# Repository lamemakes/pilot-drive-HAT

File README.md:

# The hardware of PILOT Drive

This repo contains all of the hardware for PILOT Drive - mainly KiCad schematic + PCB files, and the code used for the ATtiny85 functionality.

## The PILOT Drive HAT MKII

(**TLDR**) The features of the HAT are:
- Optocouplers to isolate & read the ACC +12v & Headlight 12v+ lines
- Via I2C the Raspberry Pi communicates with the ATtiny85 to set the shutdown time
- When there is no ACC +12v detected from the Pi or the ATtiny, the Pi begins a safe shutdown and the ATtiny begins a countdown (Longer than it would take the Pi to shutdown) to kill the power to the BAT +12v. 
- The headlight detection optocoupler is connected to the RPi's GPIO pins
- An I2C connected RTC is included to allow the Pi to keep time without network connectivity.
- Input for general purpose external buttons
- (Mostly) Conforms to the standards of the [Raspberry Pi HAT specifications](https://github.com/raspberrypi/hats), as it includes an ID EEPROM and follows most design specs, but more needs to be implemented

### HAT MKI _[& lessons learned]_

The original MKI HAT came & went. I would call it about 50% functional - as it kept time well and provided for a clean way to route power to the Pi, along with interface with buttons. It didn't work for it's original purpose though. This was due to a few reasons:
- Using tantalum caps instead of electrolytic for the power supply
- Needed decoupling caps!
- Switching the entire ground via an N-FET. Speaks for itself.
- Needed TVS diodes!

# HAT MKII

The MKII prototype was fab'd by [PCBWay](https://www.pcbway.com/), and so far has proven to be fully functional! The new improvements did volumes for the usablity, debugging, and protection of the circuit & the Pi. If you're interested, come see it's debut at the 2023 Syracuse Maker Faire on April 1st!

_The Schematic of the HAT MKII_

_Fresh MKII proto boards_

_Populated MKII proto board_

## ATtiny85 Code

### C (current) version

Found in the "firmware" folder, the current C code is based on the ATtiny85 & it's Universal Serial Interface (USI). Using I2C, the Pi can communicate the the ATtiny (default slave address is 0x20) to send a **one byte** integer (<= 255). This single integer represents the time to wait before the ATtiny pulls the power on the entire circuit after it detects the vehicle power off.

As _always_ the firmware is a WIP, and the C version isn't fully functional. I can't quite clamp why, but at the time of writing the second ACK from the ATtiny (after the one byte int) always fails. Addressing works & ACKS, the ATtiny recieves the timeout number and functions with it, but the master sees it as a failed transmission. I feel like I'm close to a fix, but stuck now.

### Arduino (legacy) version

The original firmware was written in Arduino with TinyWireS, but I believed getting a little more "bare metal" would've allowed for a lot more (needed) C & embedded learning, and allowing for quick speeds. That code can be found under "legacy" in the "firmware" folder for use until the C version is completed & smoothed over.

### To flash to the ATtiny85

This firmware requires the [avrdude](https://github.com/avrdudes/avrdude) toolchain to flash the ATtiny. With avrdude installed and an ICSP programmer connected to your ATtiny & computer, the only step left is to configure the following Makefile variables:
- ```PORT```: The serial port the ICSP device is connected to, defaults to ```/dev/ttyUSB0```
- ```AVRDUDE_CONF```: The path to your avrdude config, defauls to ```/etc/avrdude/avrdude.conf```
- ```CLK_SPEED```: Only configure if using an ATtiny85 clock speed other than 8 MHz.

### To send a timeout from to the ATtiny

This will be integrated in the [PILOT Drive software](https://github.com/lamemakes/PILOT-Drive), but an extremely simple Python script can be made to send the required timeout to a specified address, as can be seen in the example below (tested on an RPi 4):

```
import smbus

addr = 0x20 # Send to address 0x20
time = 15   # A timeout of 15 seconds

bus = smbus.SMBus(1)

bus.write_byte(addr, time)
```

At the time of writing, this script will seemingly fail, as it can't recieve a proper ACK from the ATtiny. Regardless, the ATtiny will recieve the time and respond accordingly.

### To connect a Raspberry Pi to the DS1307 RTC

**NOTE**: This guide assumes I2C has been enabled via `sudo raspi-config`

To connect the Raspberry Pi to the HAT's I2C RTC, execute the following commands on the Pi:

```
echo -e "\n# Configure the DS1307 PILOT Drive HAT\ndtoverlay=i2c-rtc,ds1307" | sudo tee -a /boot/config.txt
sudo reboot
```

After reboot, continue with the following:
```
# Ensure a "UU" appears
sudo i2cdetect -y 1

# Remove fake-hwclock
sudo apt -y remove fake-hwclock
sudo update-rc.d -f fake-hwclock remove
```

In `/lib/udev/hwclock-set`, comment out the following lines:
```
if [ -e /run/systemd/system ] ; then
    exit 0
fi
```

Write to the hardware clock:
```
# Ensure date/time is correct
date

# Write to the RTC
sudo hwclock -w

# Ensure hardware clock is correct
sudo hwclock -r
```

## NOTES:

- If building the HAT, "ID EEPROM" is recommended by Raspberry Pi [Hat Standards](https://github.com/raspberrypi/hats/blob/master/designguide.md) but aren't required to make the circuit function.
- The schematic's +5v screw terminal in refers to an external 12v to 5v buck converter. 
- KiCad library files are coming, along with 3D files for the components.
- If you're building this HAT or something similar, reach out! Would love to hear your stories.

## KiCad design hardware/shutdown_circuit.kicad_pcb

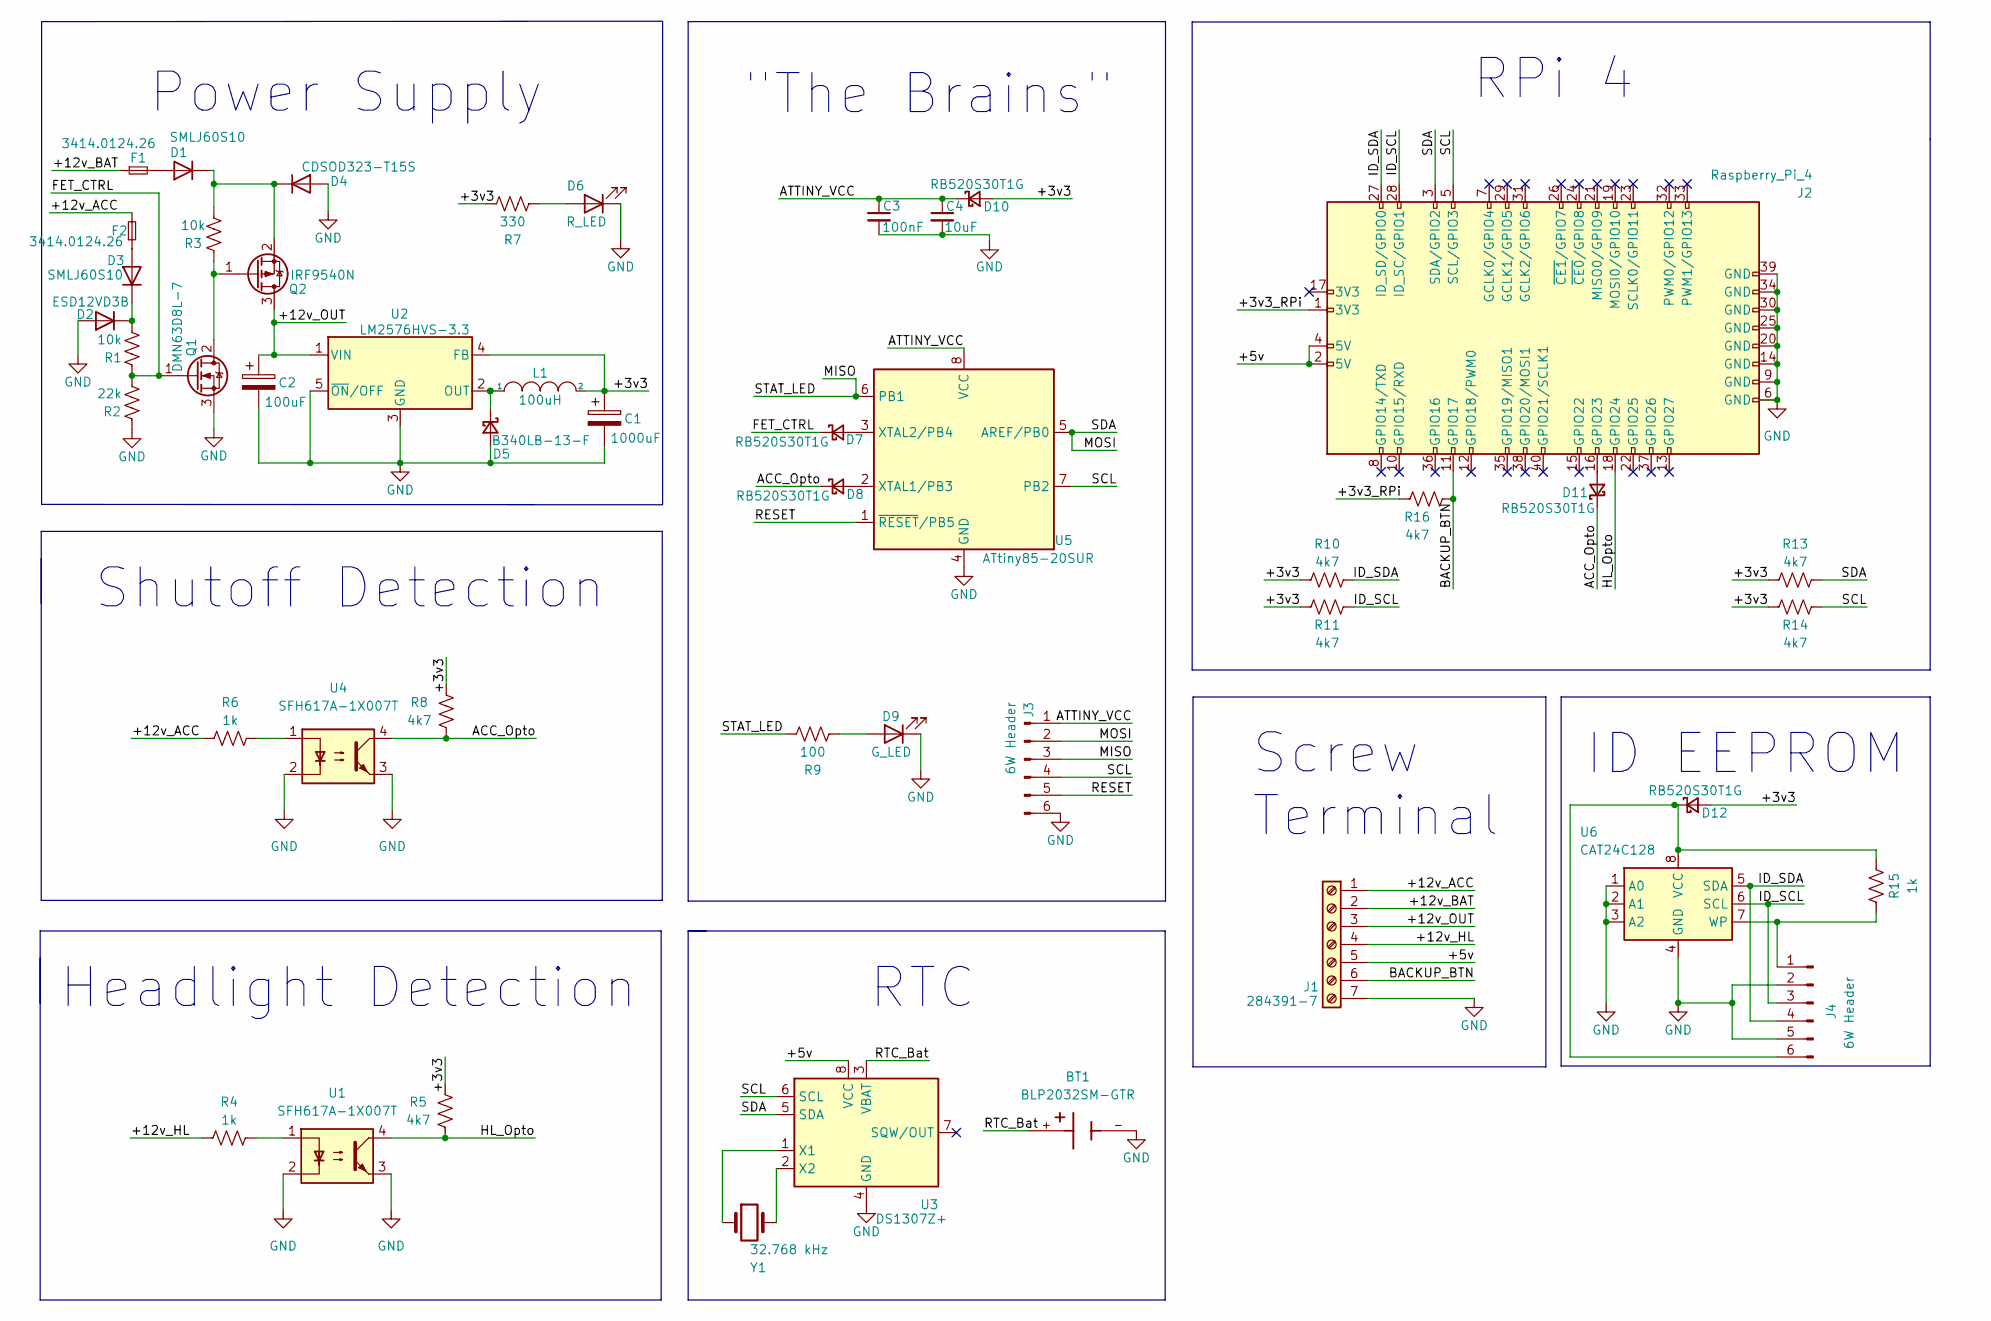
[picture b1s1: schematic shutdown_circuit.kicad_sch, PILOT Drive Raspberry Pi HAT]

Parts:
BT1: BLP2032SM-GTR; RTC_Battery_Holder; PARTREV J
C1: 1000uF; 1000uF_10v
C2: 100uF; 100uF_35v
C3: 100nF; C_0402_1005Metric_Pad0.74x0.62mm_HandSolder
C4: 10uF; C_0402_1005Metric_Pad0.74x0.62mm_HandSolder
D1, D3: SMLJ60S10; D_SMC_Handsoldering
D2: ESD12VD3B; D_SOD-323
D4: CDSOD323-T15S; D_SOD-323F
D5: B340LB-13-F; D_SMC_Handsoldering
D6: R_LED; LED_0603_1608Metric_Pad1.05x0.95mm_HandSolder
D7, D8, D10, D11, D12: RB520S30T1G; 3v3_TVS
D9: G_LED; LED_0603_1608Metric_Pad1.05x0.95mm_HandSolder
F1, F2: 3414.0124.26; Fuse_0402_1005Metric_Pad0.77x0.64mm_HandSolder
J1: 284391-7; Screw_Term
J2: Raspberry_Pi_4; PinSocket_2x20_P2.54mm_Vertical
J3, J4: 6W Header; PinHeader_1x06_P2.54mm_Vertical
L1: 100uH; 100uH_Inductor
Q1: DMN63D8L-7; N_FET
Q2: IRF9540N; P_FET
R1, R3: 10k; R_0402_1005Metric_Pad0.72x0.64mm_HandSolder
R2: 22k; R_0402_1005Metric_Pad0.72x0.64mm_HandSolder
R4, R6, R15: 1k; R_0402_1005Metric_Pad0.72x0.64mm_HandSolder
R5, R8, R10, R11, R13, R14, R16: 4k7; R_0402_1005Metric_Pad0.72x0.64mm_HandSolder
R7: 330; R_0402_1005Metric_Pad0.72x0.64mm_HandSolder
R9: 100; R_0402_1005Metric_Pad0.72x0.64mm_HandSolder
U1, U4: SFH617A-1X007T; Optocoupler
U2: LM2576HVS-3.3; TO-263-5_TabPin3
U3: DS1307Z+; DS1307Z+T&R
U5: ATtiny85-20SUR; ATTINY_SUR
U6: CAT24C128; CAT24C128YI
Y1: 32.768 kHz; RTC_Crystal

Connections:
/+3v3: C1.1, D10.2 (A), D12.2 (A), L1.2, R5.1, R7.1, R8.1, R10.2, R11.2, R13.2, R14.2, U2.4 (FB)
/+3v3_RPi: J2.1 (3V3), R16.1
/+5v: J1.5, J2.2 (5V), J2.4 (5V), U3.8 (VCC)
/+12v_ACC: F2.2, J1.1, R6.1
/+12v_BAT: F1.1, J1.2
/+12v_HL: J1.4, R4.1
/+12v_OUT: C2.1, J1.3, Q2.3 (D), U2.1 (VIN)
/ACC_Opto: D8.1 (K), D11.1 (K), R8.2, U4.4
/ATTINY_VCC: C3.1, C4.1, D10.1 (K), J3.1, U5.8 (VCC)
/BACKUP_BTN: J1.6, J2.11 (GPIO17), R16.2
/FET_CTRL: D7.1 (K), Q1.1 (G), R1.1, R2.2
/HL_Opto: J2.18 (GPIO24), R5.2, U1.4
/ID_SCL: J2.28 (ID_SC/GPIO1), J4.3, R11.1, U6.6 (SCL)
/ID_SDA: J2.27 (ID_SD/GPIO0), J4.4, R10.1, U6.5 (SDA)
/MISO: J3.3, R9.1, U5.6 (PB1)
/MOSI: J2.3 (SDA/GPIO2), J3.2, R13.1, U3.5 (SDA), U5.5 (AREF/PB0)
/RESET: J3.5, U5.1 (~RESET/PB5)
/RTC_Bat: BT1.+, U3.3 (VBAT)
/SCL: J2.5 (SCL/GPIO3), J3.4, R14.1, U3.6 (SCL), U5.7 (PB2)
GND: BT1.-, C1.2, C2.2, C3.2, C4.2, D2.2 (A), D4.2 (A), D5.2 (A), D6.1 (K), D9.1 (K), J1.7, J2.6 (GND), J2.9 (GND), J2.14 (GND), J2.20 (GND), J2.25 (GND), J2.30 (GND), J2.34 (GND), J2.39 (GND), J3.6, J4.2, J4.5, Q1.3 (S), R2.1, U1.2, U1.3, U2.3 (GND), U2.5 (~ON/OFF), U3.4 (GND), U4.2, U4.3, U5.4 (GND), U6.1 (A0), U6.2 (A1), U6.3 (A2), U6.4 (GND)
unnamed: D1.1 (K), D4.1 (K), Q2.2 (S), R3.2
unnamed: D1.2 (A), F1.2
unnamed: D2.1 (K), D3.1 (K), R1.2
unnamed: D3.2 (A), F2.1
unnamed: D5.1 (K), L1.1, U2.2 (OUT)
unnamed: D6.2 (A), R7.2
unnamed: D7.2 (A), U5.3 (XTAL2/PB4)
unnamed: D8.2 (A), U5.2 (XTAL1/PB3)
unnamed: D9.2 (A), R9.2
unnamed: D11.2 (A), J2.16 (GPIO23)
unnamed: D12.1 (K), J4.6, R15.2, U6.8 (VCC)
unnamed: J4.1, R15.1, U6.7 (WP)
unnamed: Q1.2 (D), Q2.1 (G), R3.1
unnamed: R4.2, U1.1
unnamed: R6.2, U4.1
unnamed: U3.1 (X1), Y1.1
unnamed: U3.2 (X2), Y1.2

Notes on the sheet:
Headlight Detection
RTC
Power Supply
ID EEPROM
Shutoff Detection
Screw Terminal
"The Brains"
RPi 4

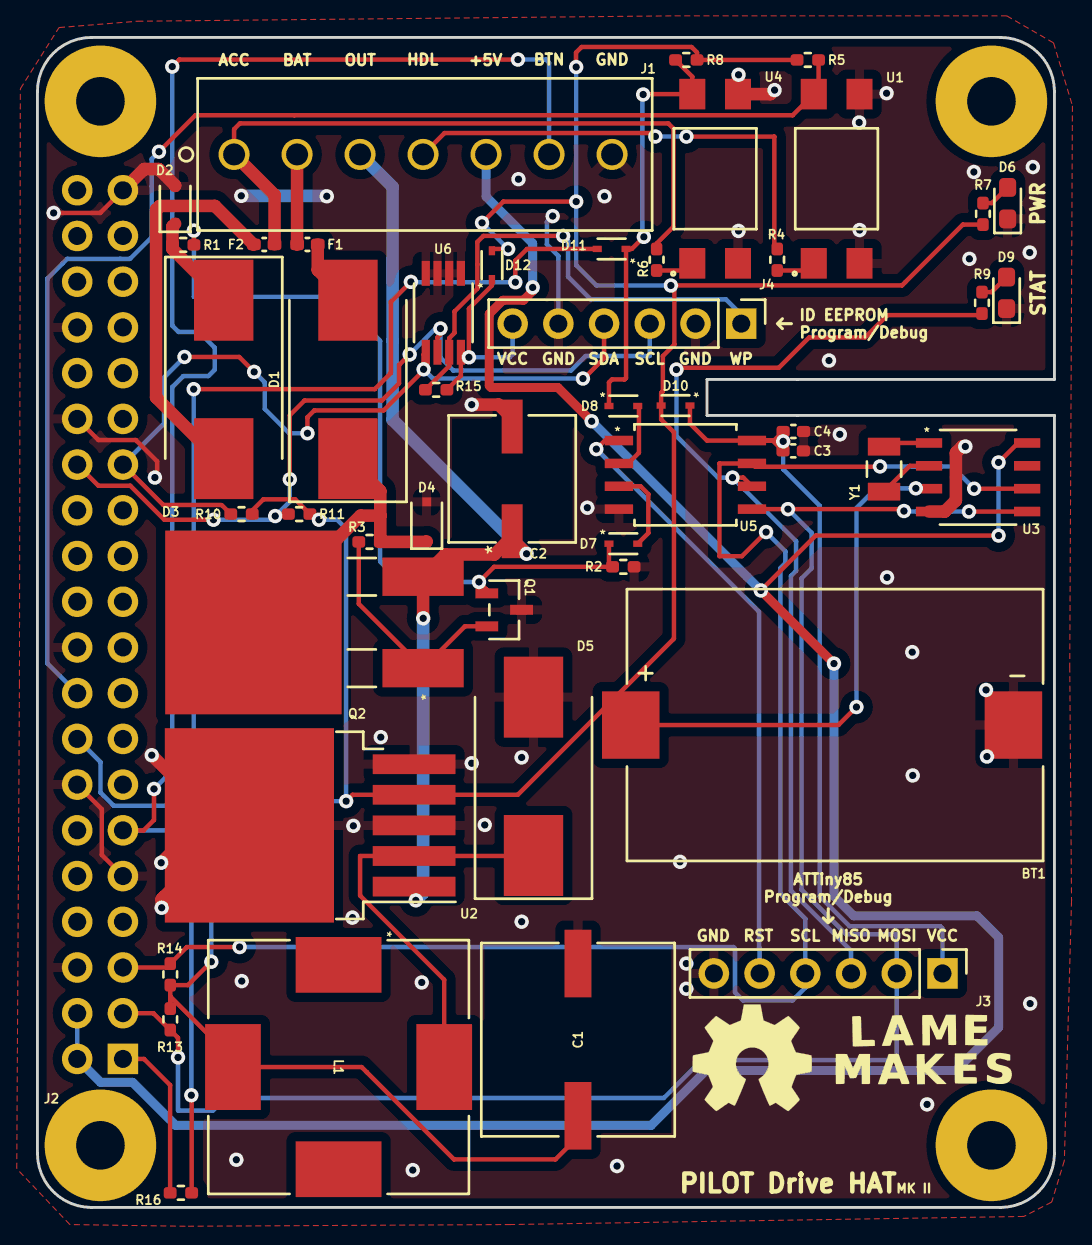
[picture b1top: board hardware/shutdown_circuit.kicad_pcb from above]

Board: 2 copper layers, 56.5 x 65.0 mm, 48 parts (1 on the bottom side), 37 nets.

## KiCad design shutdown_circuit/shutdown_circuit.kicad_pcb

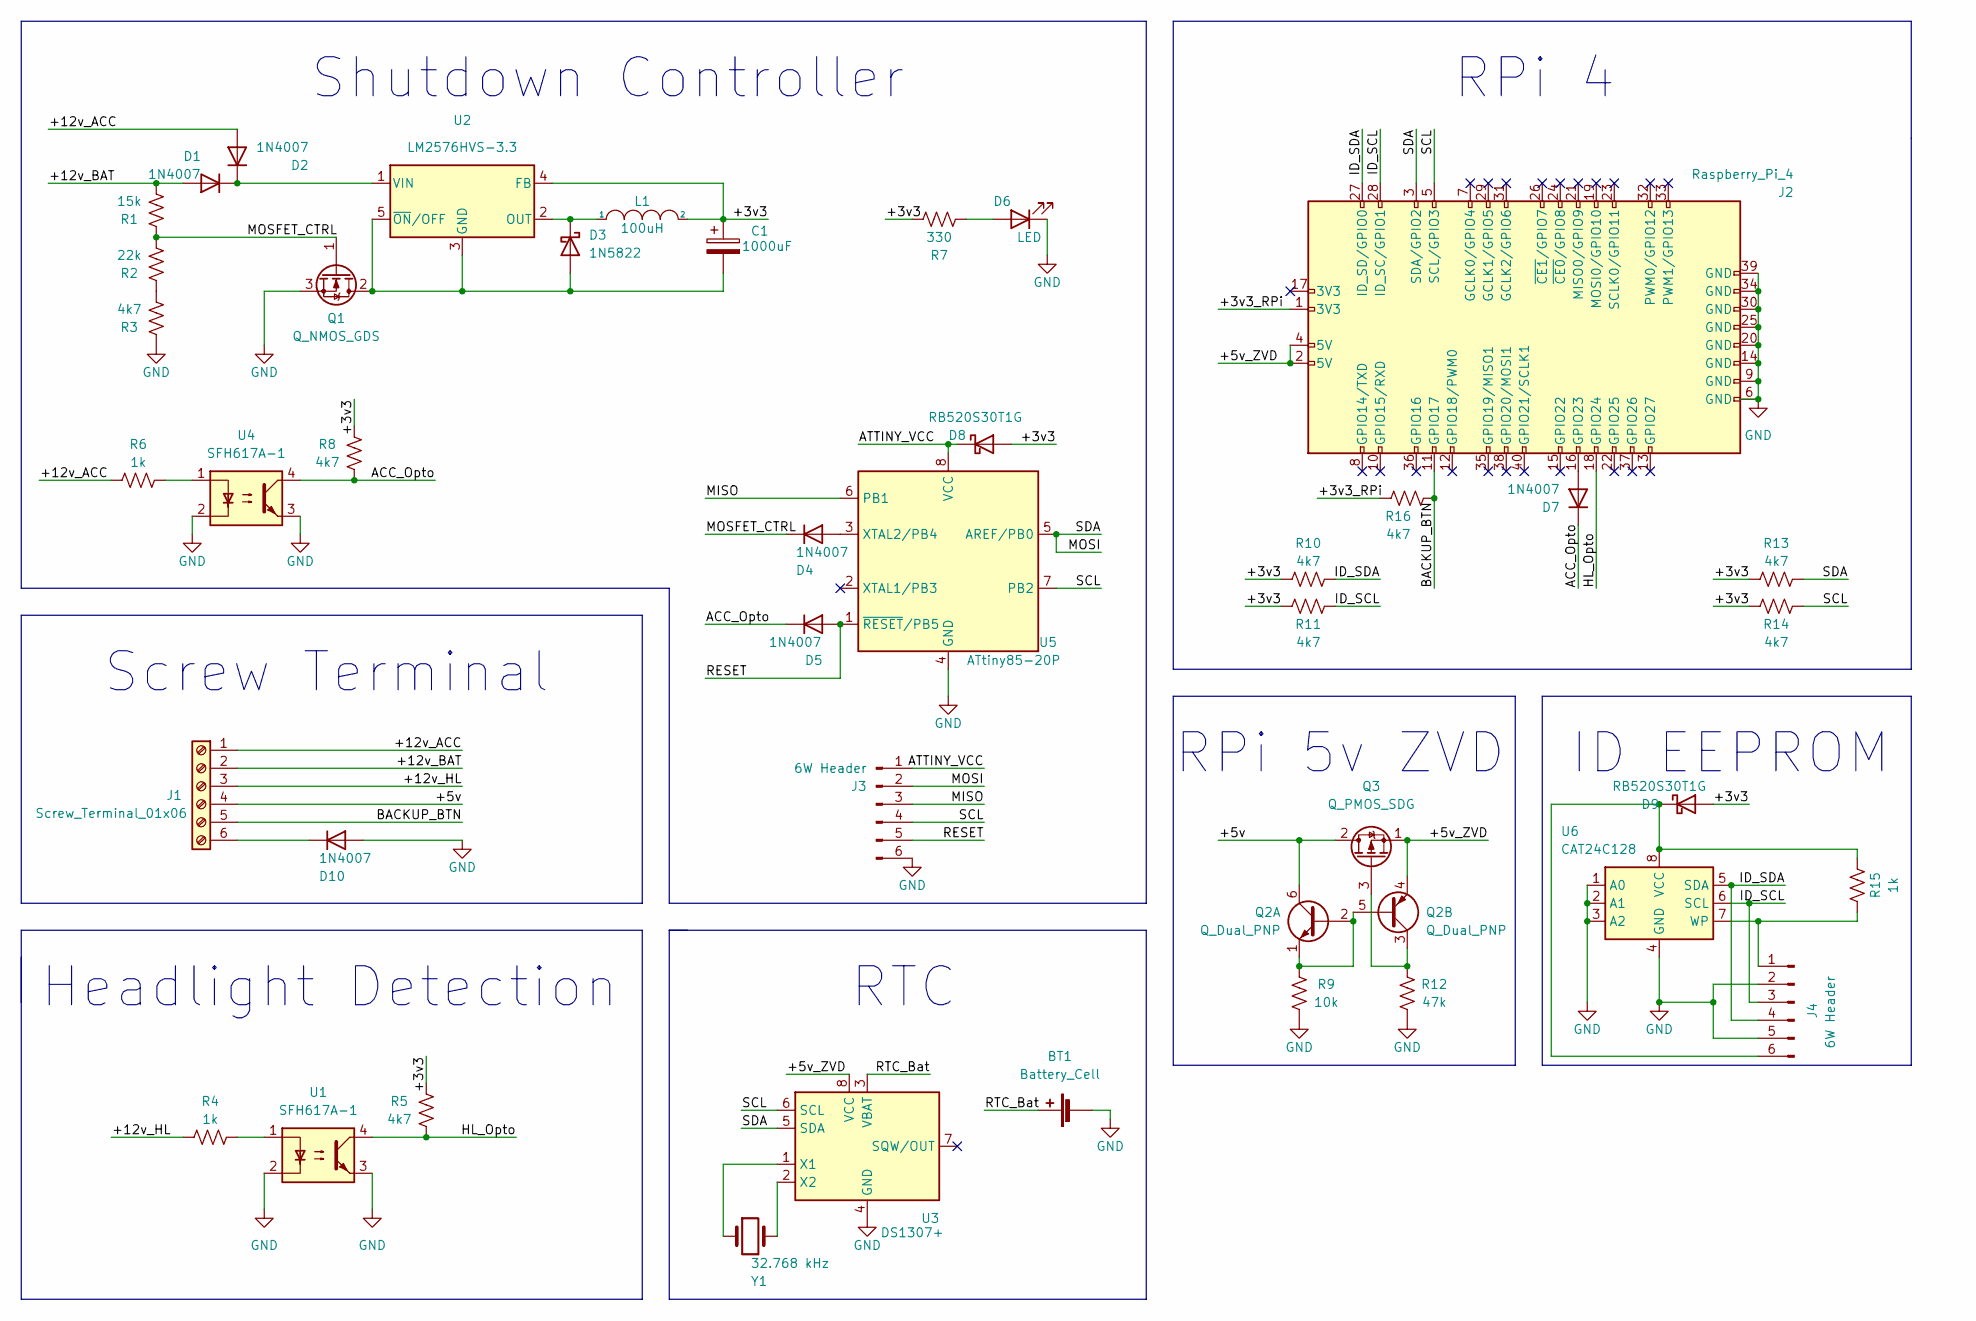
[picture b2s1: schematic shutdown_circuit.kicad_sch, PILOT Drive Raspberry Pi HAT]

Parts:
BT1: Battery_Cell; BatteryHolder_Keystone_106_1x20mm
C1: 1000uF; 100uF_Cap
D1, D2, D4, D5, D7, D10: 1N4007; 1N4007FLTR
D3: 1N5822; 1N4007FLTR
D6: LED; LED_0603_1608Metric_Pad1.05x0.95mm_HandSolder
D8, D9: RB520S30T1G; schottky_diodes
J1: Screw_Terminal_01x06; screw_term_6
J2: Raspberry_Pi_4; PinSocket_2x20_P2.54mm_Vertical
J3, J4: 6W Header; PinHeader_1x06_P2.54mm_Vertical
L1: 100uH; induct_100uH
Q1: Q_NMOS_GDS; TO-220-3_Vertical
Q2: Q_Dual_PNP; pnp_pair
Q3: Q_PMOS_SDG; zvd_mosfet
R1: 15k; R_0603_1608Metric_Pad0.98x0.95mm_HandSolder
R2: 22k; R_0603_1608Metric_Pad0.98x0.95mm_HandSolder
R3, R5, R8, R10, R11, R13, R14, R16: 4k7; R_0603_1608Metric_Pad0.98x0.95mm_HandSolder
R4, R6, R15: 1k; R_0603_1608Metric_Pad0.98x0.95mm_HandSolder
R7: 330; R_0603_1608Metric_Pad0.98x0.95mm_HandSolder
R9: 10k; R_0603_1608Metric_Pad0.98x0.95mm_HandSolder
R12: 47k; R_0603_1608Metric_Pad0.98x0.95mm_HandSolder
U1, U4: SFH617A-1; DIP-4_W7.62mm
U2: LM2576HVS-3.3; TO-263-5_TabPin3
U3: DS1307+; DIP-8_W7.62mm
U5: ATtiny85-20P; SOIC-8W_5.3x5.3mm_P1.27mm
U6: CAT24C128; TSSOP-8_4.4x3mm_P0.65mm
Y1: 32.768 kHz; Crystal_SMD_3215-2Pin_3.2x1.5mm

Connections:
/+3v3: C1.1, D8.2 (A), D9.2 (A), L1.2, R5.1, R7.1, R8.1, R10.2, R11.2, R13.2, R14.2, U2.4 (FB)
/+3v3_RPi: J2.1 (3V3), R16.1
/+5v: J1.4, Q2.6 (C1), Q3.2 (D)
/+5v_ZVD: J2.2 (5V), J2.4 (5V), Q2.4 (E2), Q3.1 (S), U3.8 (VCC)
/+12v_ACC: D2.2 (A), J1.1, R6.1
/+12v_BAT: D1.2 (A), J1.2, R1.2
/+12v_HL: J1.3, R4.1
/ACC_Opto: D5.1 (K), D7.1 (K), R8.2, U4.4
/ATTINY_VCC: D8.1 (K), J3.1, U5.8 (VCC)
/BACKUP_BTN: J1.5, J2.11 (GPIO17), R16.2
/HL_Opto: J2.18 (GPIO24), R5.2, U1.4
/ID_SCL: J2.28 (ID_SC/GPIO1), J4.3, R11.1, U6.6 (SCL)
/ID_SDA: J2.27 (ID_SD/GPIO0), J4.4, R10.1, U6.5 (SDA)
/MISO: J3.3, U5.6 (PB1)
/MOSFET_CTRL: D4.1 (K), Q1.1 (G), R1.1, R2.2
/RESET: D5.2 (A), J3.5, U5.1 (~RESET/PB5)
/RTC_Bat: BT1.1 (+), U3.3 (VBAT)
/SCL: J2.5 (SCL/GPIO3), J3.4, R14.1, U3.6 (SCL), U5.7 (PB2)
/SDA: J2.3 (SDA/GPIO2), J3.2, R13.1, U3.5 (SDA), U5.5 (AREF/PB0)
GND: BT1.2 (-), D6.1 (K), D10.2 (A), J2.6 (GND), J2.9 (GND), J2.14 (GND), J2.20 (GND), J2.25 (GND), J2.30 (GND), J2.34 (GND), J2.39 (GND), J3.6, J4.2, J4.5, Q1.3 (S), R3.1, R9.2, R12.2, U1.2, U1.3, U3.4 (GND), U4.2, U4.3, U5.4 (GND), U6.1 (A0), U6.2 (A1), U6.3 (A2), U6.4 (GND)
unnamed: C1.2, D3.2 (A), Q1.2 (D), U2.3 (GND), U2.5 (~ON/OFF)
unnamed: D1.1 (K), D2.1 (K), U2.1 (VIN)
unnamed: D3.1 (K), L1.1, U2.2 (OUT)
unnamed: D4.2 (A), U5.3 (XTAL2/PB4)
unnamed: D6.2 (A), R7.2
unnamed: D7.2 (A), J2.16 (GPIO23)
unnamed: D9.1 (K), J4.6, R15.2, U6.8 (VCC)
unnamed: D10.1 (K), J1.6
unnamed: J4.1, R15.1, U6.7 (WP)
unnamed: Q2.1 (E1), Q2.2 (B1), Q2.5 (B2), R9.1
unnamed: Q2.3 (C2), Q3.3 (G), R12.1
unnamed: R2.1, R3.2
unnamed: R4.2, U1.1
unnamed: U3.1 (X1), Y1.1
unnamed: U3.2 (X2), Y1.2
unnamed: R6.2, U4.1

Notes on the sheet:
Headlight Detection
RTC
Shutdown Controller
ID EEPROM
RPi 5v ZVD
Screw Terminal
RPi 4

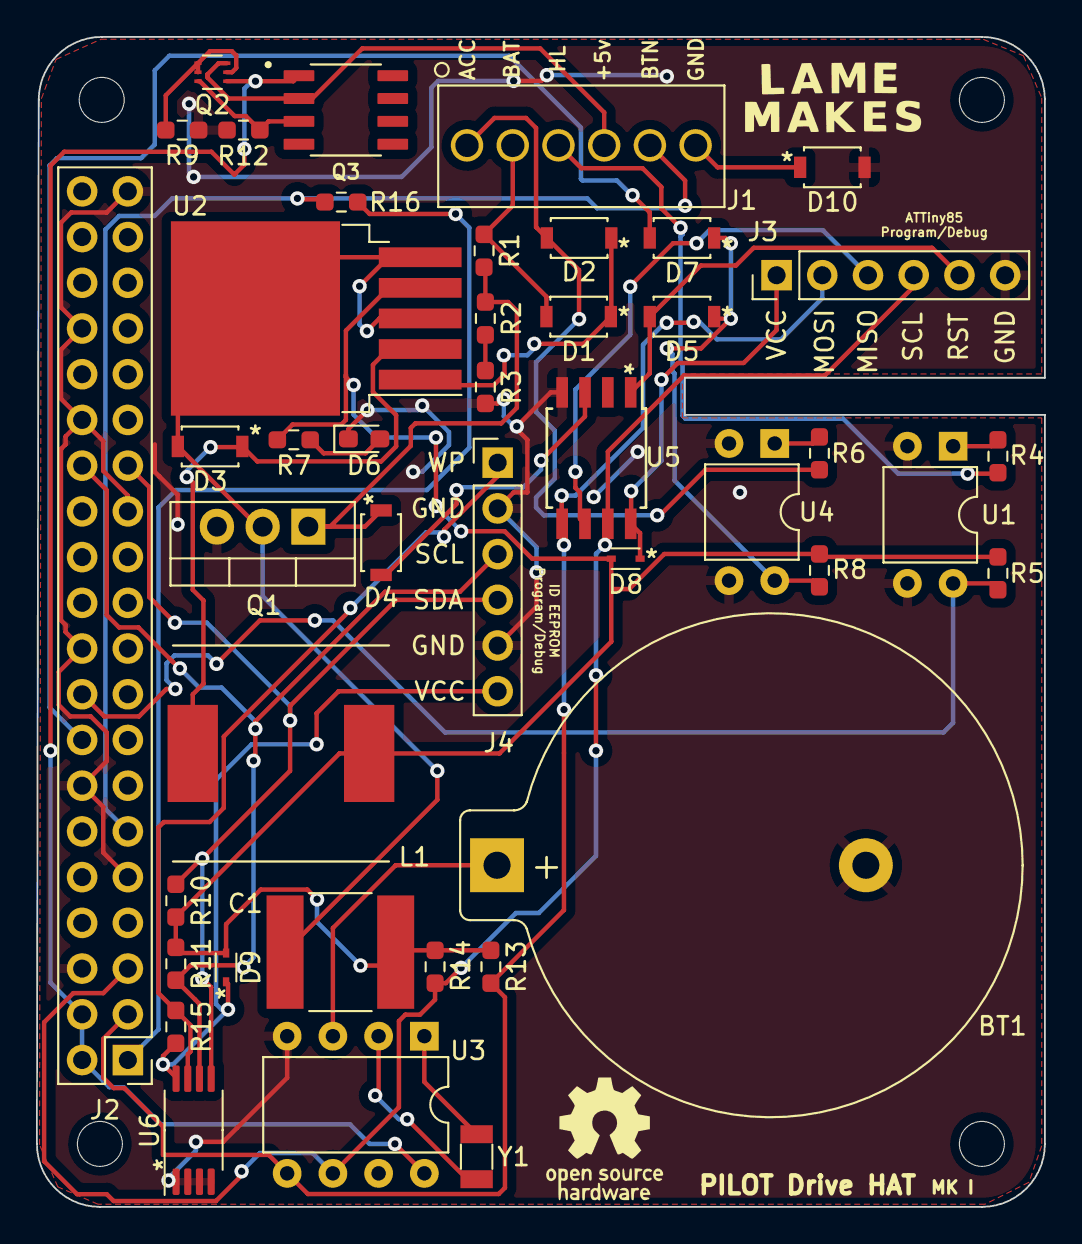
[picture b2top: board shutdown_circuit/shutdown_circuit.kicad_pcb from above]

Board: 2 copper layers, 56.0 x 65.0 mm, 43 parts (0 on the bottom side), 36 nets.

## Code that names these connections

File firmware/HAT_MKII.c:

#include <avr/io.h>PORTB
#include <avr/interrupt.h>
#include <util/delay.h>
#include "HAT_MKII.h"


/*
PB4 = MOSFET control (high is powered, low kills the circuit)   | Output
PB3 = Accessory Wire Optocoupler (pulled low when active)       | Input
PB2 = SCL                                                       | Input
PB1 = Status LED                                                | Output
PB0 = SDA                                                       | Input

INIT_DDRB shifts bits accordingly to input/output.
*/


void led_blink(int ledPb, int times){
    for (int i = 0; i < times; i++){
        PORTB ^= (1 << ledPb);
        _delay_ms(500);
        PORTB ^= (1 << ledPb);
        _delay_ms(500);
    }
}

void initialize()
{
    // Setup the needed PILOT Drive HAT pins
    DDRB = initDDRB;
    PORTB = (1 << FET_CTL) | (1 << ACC_OPTO); // Pullup ACC optocoupler pin & power the FET.

    // Setup I2C in the USI interface
    USICR = (1 << USIWM1) | (1 << USICS0) | (1 << USICS1);  // Set USI interface to I2C, and clock to external w negative edge sampling.
    //DDRB &= (1 << 2) | (1 << 0); // SDA & SCL direction as input

    led_blink(STATUS_LED, 1);
}

void send_ack() {
    USISR |= (1 << USIOIF);
    DDRB |= (1 << 0);  // Initialize the SDA Data Direction Bit
    int clkMask = (1 << USICNT3) | (1 << USICNT2) | (1 << USICNT1) | (1 << USICNT0);
    if (!byte) {    // If this is the first byte...
        USISR &= clkMask;
        while ((USISR & clkMask) <= (1 << USICNT2)) { // While the counter is <= 4, BUT greater than 2. An extra clock cycle is missed with the address bits, not sure why? Maybe start cond?
            if (USISR & clkMask >= (1 << USICNT1)){
                PORTB |= (1 << SDA); // Drive SDA
            }
        }
    } else if (byte > 0) {
        USISR &= clkMask;
        while ((USISR & clkMask) < (1 << 0)) { // While the counter is < 1
            PORTB |= (1 << SDA); // Drive SDA
        }
    }
    //PORTB &= ~(1 << 0); // Stop SDA drive & change data direction
    DDRB &= ~(1 << 0);
    USISR = 0; // Reset counter
}

void recieve_data(){
    int dataIn = USIBR / 2; // It appears the external clock is sampled on BOTH (pos/neg) edges, thus gets double the intended value?
    if (!byte && (dataIn == SLAVE_ADDR)){ // If this is the first byte & the buffer == slave address...
        read_data = 1;  // Set data read to true.
        send_ack();
    } else if (byte){
        timeout = dataIn;
        send_ack();
        read_data = 0;
        data_recieved = 1;
    }

}

int main (void){

    initialize();

    while(1){
        if ((USISR & (1 << 7)) == (1 << 7)){    // Check if the 7th bit of USISR (start condition register) is a 1
            USISR = (1 << 7); // Clear start condition flag & reset counter
            while ((USISR & (1 << 5)) != (1 << 5)){ // While theres no stop (USIPF) condition...
                if ((!byte) || ((2 > byte > 0) && (read_data))){    // Only move to recieve if the first byte is being set (addressing) or if the address has already been read & validated.
                    if ((USISR & (1 << 6)) == (1 << 6)) {   // Check if the 6th bit of USISR (Counter Overflow Interrupt) is a 1
                        recieve_data();
                        byte++;
                    }
                }
            }
            USISR |= (1 << 5); // Clear the stop condition flag (USIPF)
            _delay_ms(1000);
            if (data_recieved) {
                led_blink(STATUS_LED, 2);
                data_recieved = 0;
            }
            byte = 0;
        }
        if ((PINB & (1 << ACC_OPTO)) == (1 << ACC_OPTO)) { // If ACC is pulled high (car shut off)
            int time_count = 0;
            PORTB |= (1 << STATUS_LED);   // Turn on the LED to indicate an impending shutdown
            while ((PINB & (1 << ACC_OPTO)) == (1 << ACC_OPTO)) { // Keep checking that the car doesn't turn back on, quit if it does
                _delay_ms(1000);
                time_count++;
                //PORTB ^= (1 << STATUS_LED);
                if (time_count == timeout) {
                    PORTB &= ~(1 << FET_CTL);  // Kill circuit power by toggling the FET pin
                }
            }
            PORTB &= ~(1 << STATUS_LED);  // Turn off the LED, shutdown is canceled.
        }
    }
}

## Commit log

2022-09-07 Quick & dirty file upload
    All of these will be extended on moving forward, just wanted something in the books 😎
2022-09-07 README
2022-10-09 Updated KiCad schematic
    ...to include mosfet as a relay replacement & (some) HAT standard implementations such as I2C EEPROM
2022-10-10 Added I2C functionality
2022-10-14 schematic update
2022-10-16 Schematic updated to conform to HAT standards + use nets
2022-10-16 Schematic typo fix
2022-10-16 Made schematic conform to HAT standards + added nets
2022-10-16 Notes updates
2022-10-16 More small schematic error fixes
2022-10-26 PCB Updates
2022-10-28 SPI added instead of I2C for ATTINY85 programmer
2022-10-28 Schematic, PCB, and netlist upload
2022-10-28 pilot drive footprints
2022-11-15 Update PILOT_Drive_ATTiny85.ino
    Typo
2023-01-09 Updated for HAT MKII & new firmware
2023-01-09 typo :0
2023-01-10 Added actual firmware & updated README
2023-01-10 Fixed some comments along with KiCad schmatic updates
2023-01-10 Updated schematic & schematic screenshots
2023-01-10 more minor readme updates
2023-01-13 Added Licenses
2023-02-22 PILOT Drive HAT MKII
2023-03-04 Post-MKII Prototype fixes
2023-03-04 Updated photos & README for MKII
2023-03-08 PCB Typo fixes
2023-03-17 PCBWay link
2023-07-05 Added better silkscreen text
2023-07-12 README RTC updates

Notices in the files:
parts and their libraries:
Copyright 2021 Accelerated Designs. All rights reserved.
